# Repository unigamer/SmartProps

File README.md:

SmartProps
==========

Smart LED circus props

Demo: https://www.youtube.com/watch?v=CMix5ZxQXCQ&feature=youtu.be

You want open source, smart, bluetooth enabled, LED juggling props?! Well, you're at the right place. However, this project is very much in its infancy. You can't buy any props and even making them is a bit tricky just now. I still think the code should be available so it's all here.

What can your juggling balls do?
The juggling balls are wirelessly connected and can detect if they are in your hand or in the air. A simple effect is changing colour every time they are thrown. A more advanced version is when all balls thrown at an instance change to the same random colour. The balls can flash and fade as well as staying a solid colour. All of this can be controlled through your computer or bluetooth-enabled Android phone. No more annoying button tapping to program your props! :)

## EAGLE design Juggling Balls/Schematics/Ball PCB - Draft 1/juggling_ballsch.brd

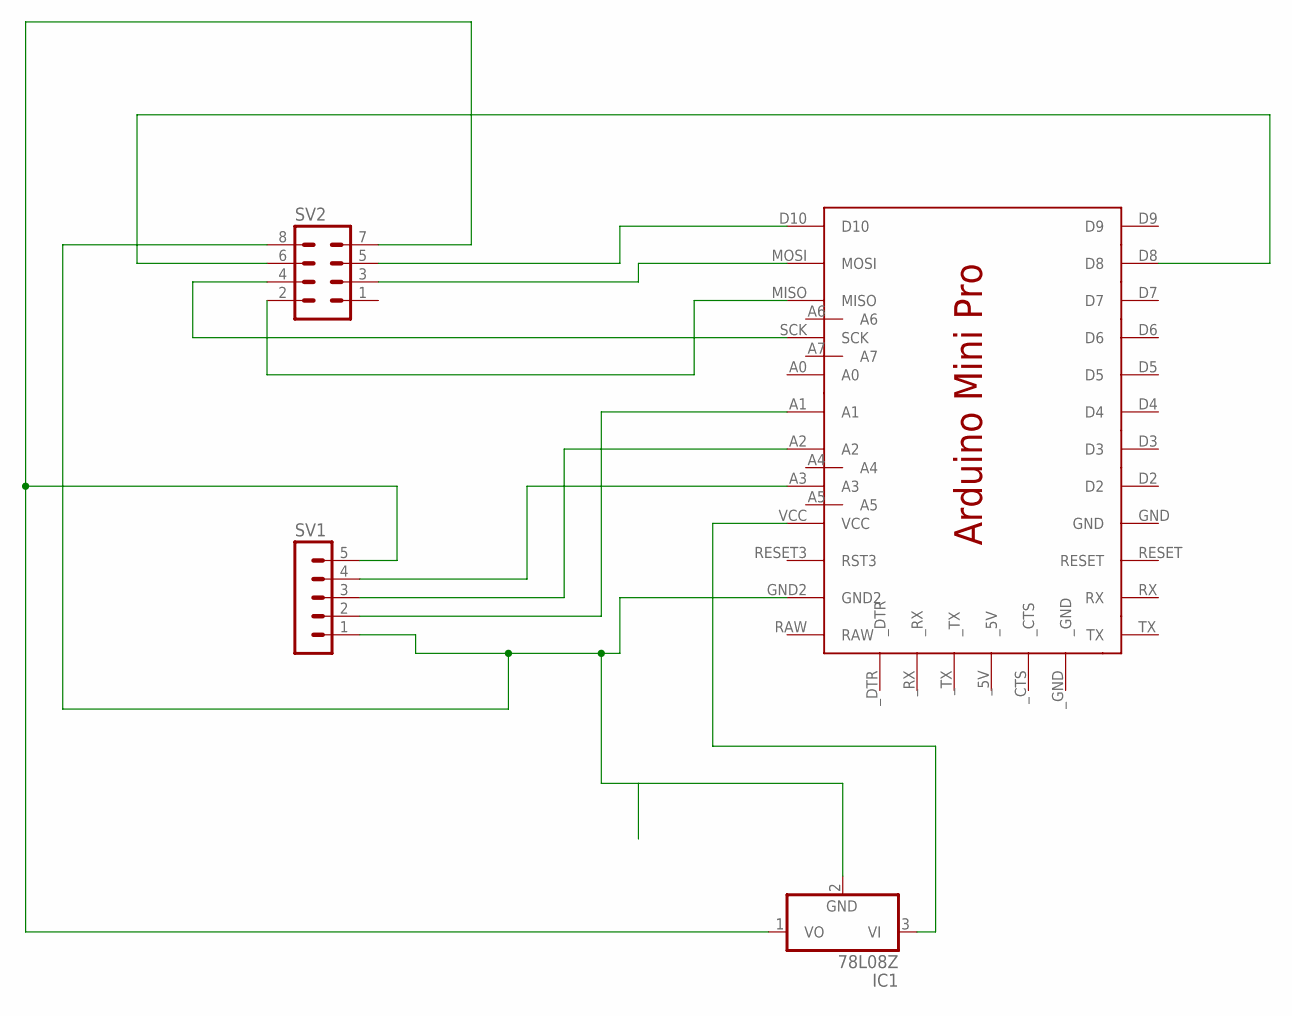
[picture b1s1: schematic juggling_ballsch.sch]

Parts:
IC1: 78L08Z; TO92
SV1: MA05-1
SV2: MA04-2
U$1: ARDMINIPRO

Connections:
unnamed: SV1.2, U$1.A1
unnamed: SV1.3, U$1.A2
unnamed: SV1.4, U$1.A3
unnamed: IC1.2 (GND), SV1.1, SV2.8, U$1.GND2
unnamed: SV2.3, U$1.MOSI
unnamed: SV2.5, U$1.D10
unnamed: SV2.2, U$1.MISO
unnamed: SV2.6, U$1.D8
unnamed: SV2.4, U$1.SCK
unnamed: IC1.1 (VO), SV1.5, SV2.7
unnamed: IC1.3 (VI), U$1.VCC

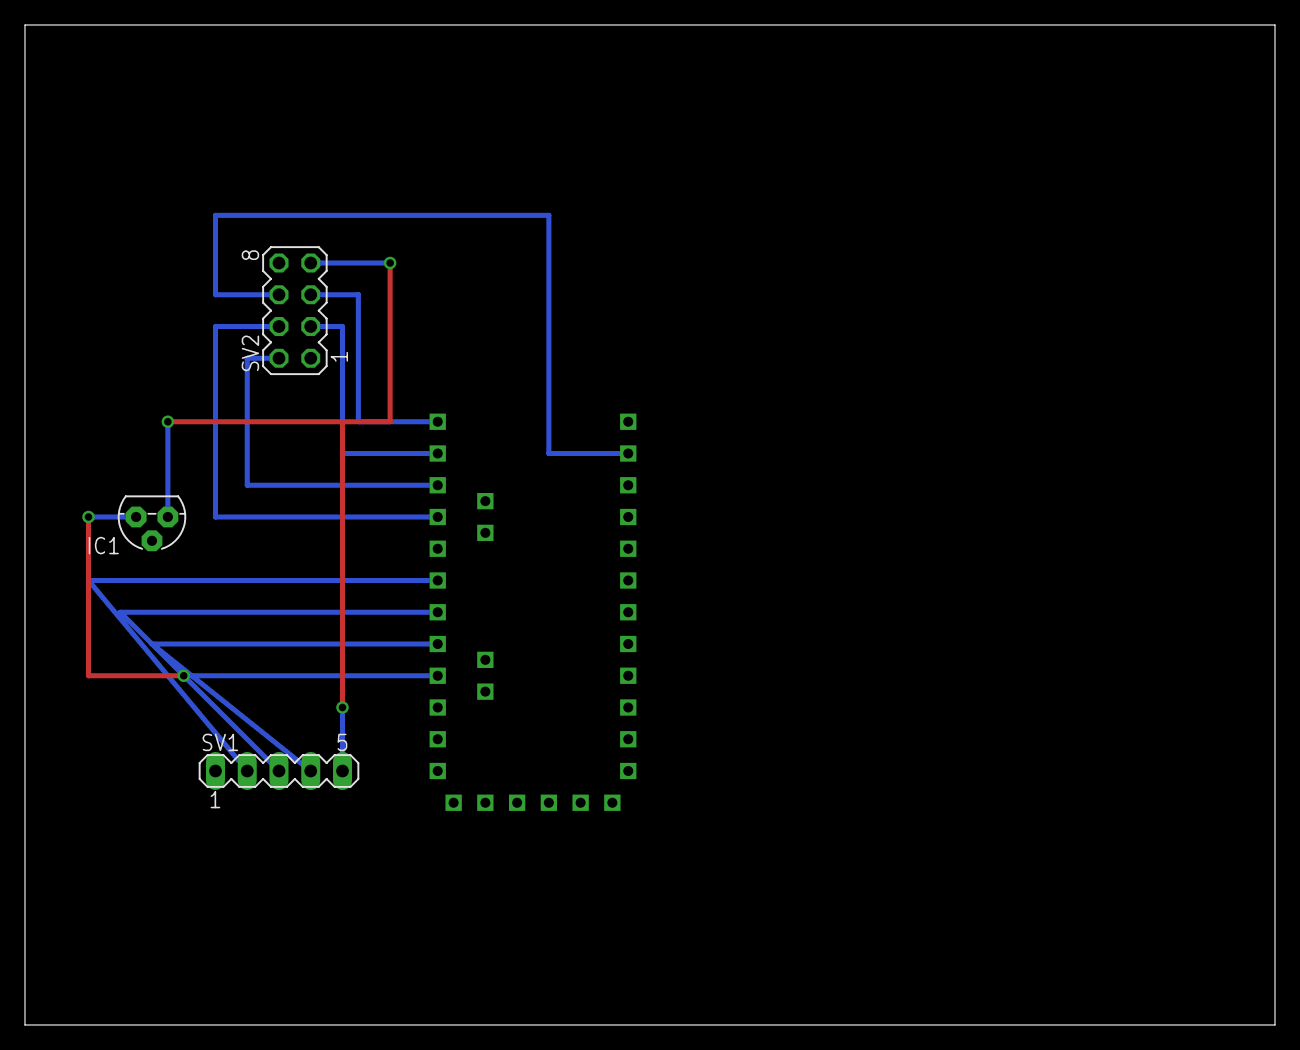
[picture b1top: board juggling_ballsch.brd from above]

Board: 2 copper layers, 100.0 x 80.0 mm, 4 parts (0 on the bottom side), 11 nets.

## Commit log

2014-04-22 Test Commit
    Testing the commit
2014-04-22 Another test
    Another Test
2014-04-22 Adding License
    Added GPL v2 License
    http://choosealicense.com/licenses/gpl-v2/
2014-04-22 First bulk upload of code
    This is the first major upload of code. Not exactly well tested, but it
    should all be here!
2014-04-22 Change some folder names
    Fiddling around with stuff
2014-04-25 Fixed "Throw Random Sync"
    I had moved Throw Random Sync to effects.ino and because it was outisde
    the main loop payload_tx.p1 wasn't available so the colour wasn't being
    sent back to the ball.
    Should be fixed now.
2014-04-28 Added link to demo video
